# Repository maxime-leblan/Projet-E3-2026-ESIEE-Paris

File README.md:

# VigiZone : Prévention des collisions engins-piétons sur chantiers

*Remise du prix du meilleur projet technique lors du [Jour des Projets](https://jdp.esiee.fr) E3 2026 à ESIEE Paris*

### Membres de l'équipe

Nous étions une équipe de 6 étudiants en 1ère année du cycle ingénieur à ESIEE Paris
*dans l'ordre de droite à gauche :*
* Hugues JOUHAUD
* Naïm BEN-RAÏES
* Benoît DE KEYN
* Maxime LE BLAN
* Clarisse BLONDEL
* Jérémy FOUILLOUX

 Suivis par notre tutrice **Mme Ting WANG**, assistante professeur de robotique à ESIEE PARIS, nous avons reçu le prix du meilleur projet technique de la part du jury technique **M. Denis BUREAU** (tout à gauche sur la photo), professeur d'informatique à ESIEE Paris.

**[Lire le rapport complet du projet VigiZone (PDF)](https://drive.google.com/uc?export=download&id=16rXCA4nlOrGEzkfiPZYJjSept83bqB7f)**

---

## Contexte : Un enjeu de sécurité vital

Le secteur du Bâtiment et des Travaux Publics (BTP) fait face à des risques majeurs concernant la sécurité de ses travailleurs.
* Les collisions entre les engins de chantier et les ouvriers piétons représentent la première cause d'accidents mortels dans ce domaine.
* Selon l'Organisme Professionnel de Prévention du Bâtiment et des Travaux Publics (OPPBTP), on dénombre environ quinze décès par an causés par ces collisions.

Initialement, notre équipe souhaitait développer un dispositif pour les travailleurs isolés. Cependant, des échanges avec Monsieur Luc-Géry Helle, directeur régional génie civil de GTM Ouest (VINCI Construction France), ont mis en lumière une contrainte réglementaire stricte : la législation française interdit ou encadre très fortement le travail isolé sur les chantiers de construction. Le projet a donc été réorienté pour répondre au besoin critique de la prévention des collisions.

---

## Qu'est-ce que VigiZone ?

VigiZone est un système embarqué de détection en temps réel conçu pour éviter les collisions entre les ouvriers et les véhicules de chantier. 

Face à ce danger, les systèmes d'alarme sonores classiques (comme les bips de recul) perdent en efficacité, car les ouvriers s'habituent au bruit ambiant. De leur côté, les solutions basées sur des caméras IA ou des capteurs LiDAR sont extrêmement coûteuses et voient leurs performances chuter dans des conditions difficiles (poussière, boue, faible luminosité). 

C'est pourquoi VigiZone s'appuie sur la technologie **Ultra Wide Band (UWB)** :
* L'UWB offre une très haute précision de positionnement en se basant sur le temps de vol du signal.
* C'est un signal robuste capable de bien traverser les obstacles.

---

## Architecture et Utilisation

Le fonctionnement de VigiZone repose sur la communication entre trois sous-systèmes interdépendants :

* **Le Hub central (Unité de bord) :** Placé dans la cabine du conducteur et alimenté par la batterie de l'engin, il fusionne les données pour calculer les distances par trilatération. 

  Il est équipé d'un écran permettant de localiser les ouvriers en direct par rapport à une zone de danger et d'une alarme sonore.

* **Les Ancres (Boîtiers véhicule) :** Quatre capteurs disposés sur l'armature de l'engin (par exemple, aimantés) qui servent à localiser les ouvriers.
* **Le Tag (Boîtier ouvrier) :** Un équipement de protection individuelle (EPI) compact porté par l'ouvrier (sur son casque ou à la ceinture). Afin de garantir la sécurité, il ne possède aucun bouton d'arrêt et s'allume automatiquement.

**Scénario d'utilisation :** Si un ouvrier équipé d'un Tag pénètre dans une zone de danger virtuelle délimitée autour de l'engin, le système alerte instantanément les deux parties. Le conducteur est averti par l'écran et une alarme en cabine, tandis que le Tag de l'ouvrier déclenche une alerte sonore suffisamment puissante pour couvrir le bruit du chantier.

---

## Limites et Nuances du Système

Bien que la technologie UWB apporte une grande fiabilité de détection, notre solution technique ne prétend pas résoudre entièrement le problème des accidents. 

Comme nous l'a expliqué Monsieur Mathieu Baré, directeur prévention délégation génie civil Ouest chez VINCI Construction France, lors de notre visite sur le chantier du Grand Paris Express : plusieurs dispositifs de prévention existent, mais chacun possède ses avantages et ses limites selon les situations. À ce jour, aucun système ne permet de supprimer complètement le risque de collision entre engins et piétons. VigiZone doit donc être perçu comme un outil d'assistance et une couche de sécurité supplémentaire, qui vient compléter, mais en aucun cas remplacer, la vigilance indispensable des conducteurs et des ouvriers.

---

## En savoir plus

Pour consulter l'intégralité de notre démarche (choix technologiques, algorithmes de trilatération, conception des cartes sous KiCad et analyse éthique), nous vous invitons à lire notre rapport complet.

**[Lire le rapport complet du projet VigiZone (PDF)](https://drive.google.com/uc?export=download&id=16rXCA4nlOrGEzkfiPZYJjSept83bqB7f)**

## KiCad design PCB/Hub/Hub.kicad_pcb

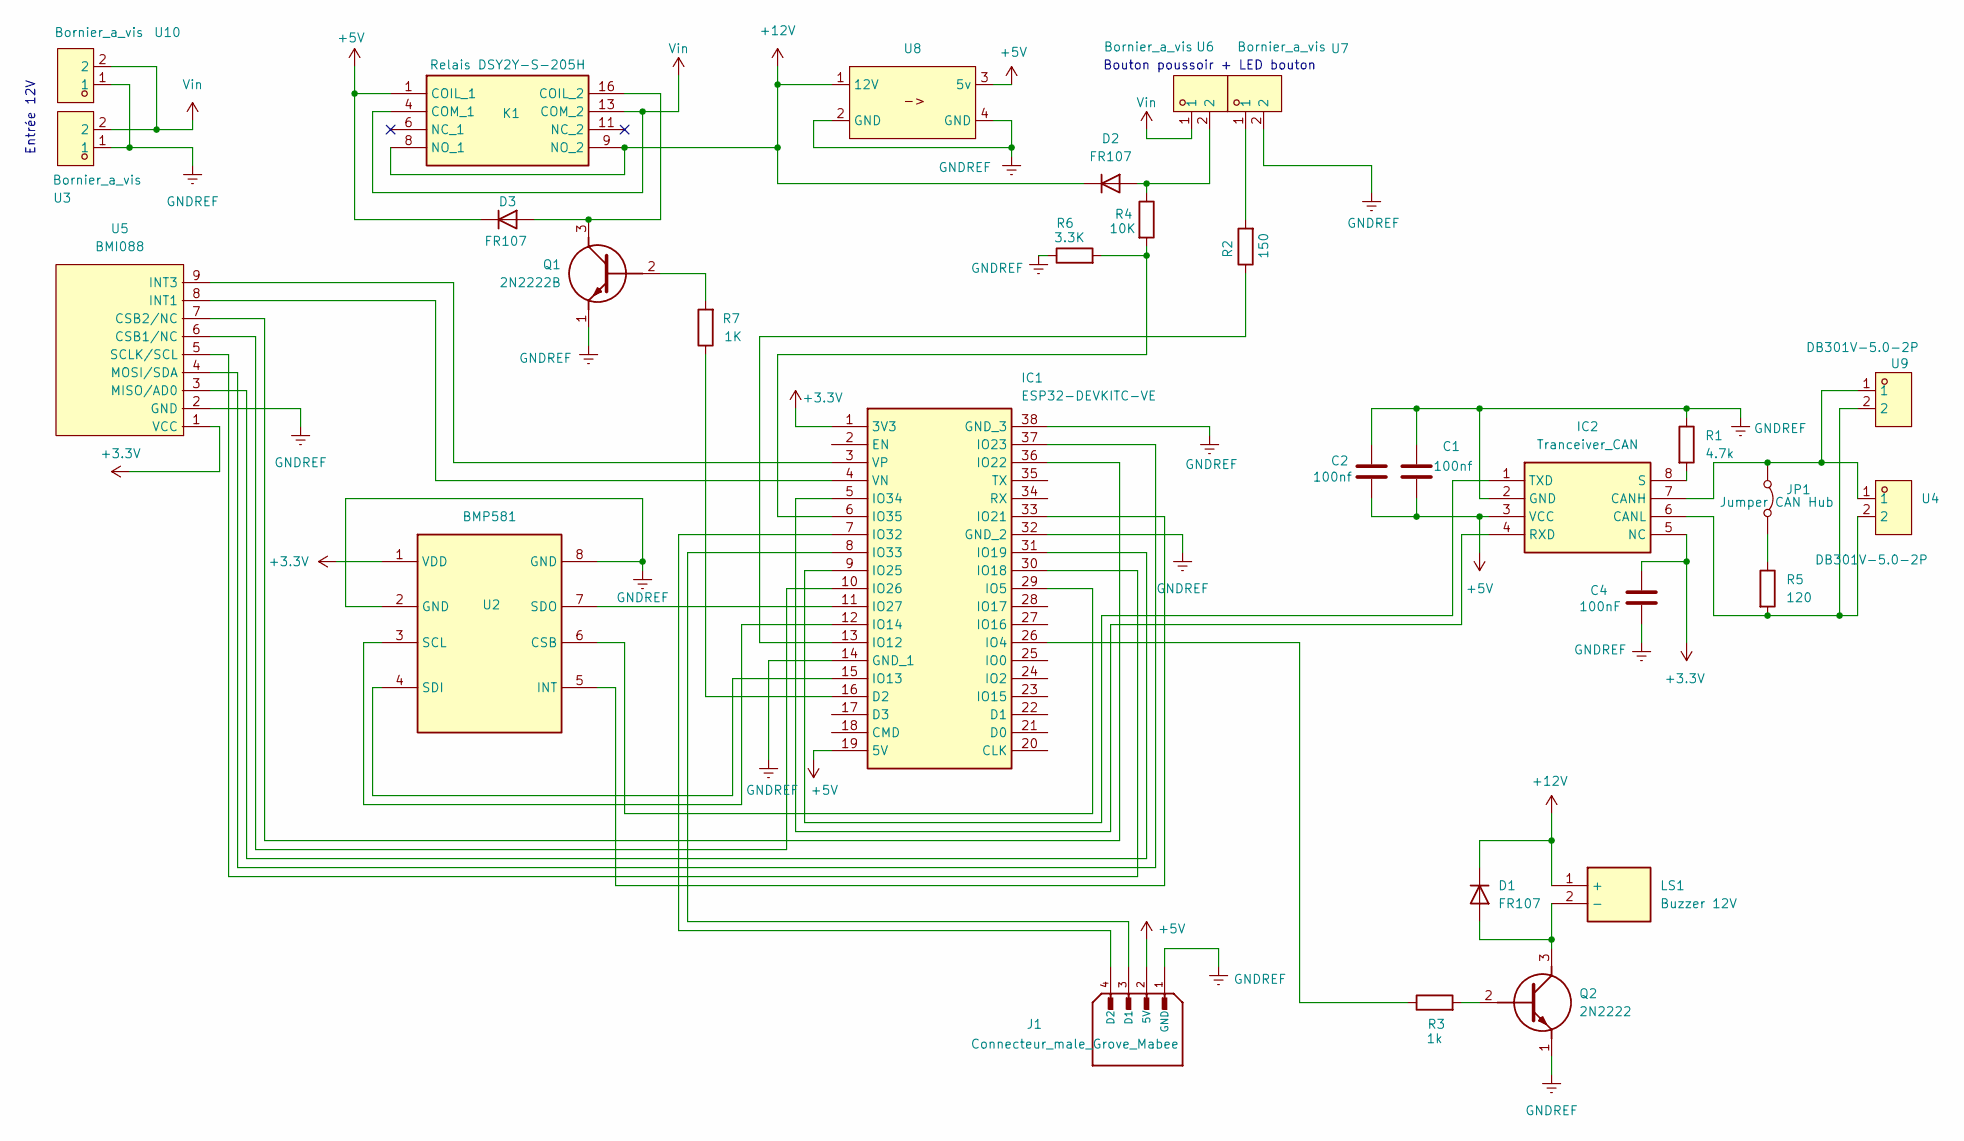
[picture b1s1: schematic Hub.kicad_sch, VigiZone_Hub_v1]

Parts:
C1, C2: 100nf; C_Axial_L3.8mm_D2.6mm_P7.50mm_Horizontal
C4: 100nF; C_0402_1005Metric_Pad0.74x0.62mm_HandSolder
D1, D2, D3: FR107; Diode FR107
IC1: ESP32-DEVKITC-VE; ESP32-WROVER DevKitC; Manufacturer_Part_Number ESP32-DEVKITC-VE; Mouser Part Number 356-ESP32-DEVKTC32VE
IC2: Tranceiver_CAN; Tranceiver CAN; Manufacturer_Part_Number TCAN1051VDRQ1; Mouser Part Number 595-TCAN1051VDRQ1
J1: Connecteur_male_Grove_Mabee; Connecteur male Grove_Mabee; PARTREV N/A
JP1: Jumper CAN Hub; Jumper CAN hub
K1: Relais DSY2Y-S-205H; Manufacturer_Part_Number DSY2Y-S-205L
LS1: Buzzer 12V; Manufacturer_Part_Number CMT-8504-100-SMT-TR; Mouser Part Number 490-CMT-8504100SMTTR
Q1: 2N2222B; Mouser Part Number 637-2N2222A
Q2: 2N2222; 2N2222B; Mouser Part Number 637-2N2222A
R1: 4.7k; R_Axial_DIN0207_L6.3mm_D2.5mm_P10.16mm_Horizontal
R2: 150; R_Axial_DIN0207_L6.3mm_D2.5mm_P10.16mm_Horizontal
R3: 1k; R_Axial_DIN0207_L6.3mm_D2.5mm_P10.16mm_Horizontal
R4: 10K; R_Axial_DIN0207_L6.3mm_D2.5mm_P10.16mm_Horizontal
R5: 120; R_Axial_DIN0207_L6.3mm_D2.5mm_P10.16mm_Horizontal
R6: 3.3K; R_Axial_DIN0207_L6.3mm_D2.5mm_P10.16mm_Horizontal
R7: 1K; R_Axial_DIN0207_L6.3mm_D2.5mm_P10.16mm_Horizontal
U2: BMP581; Manufacturer_Part_Number BMP581; Mouser Part Number 262-BMP581
U3, U6, U7, U10: Bornier_a_vis; Bornier a vis; MPN DB301V-5.0-2P-BU-S; LCSC Part C395882
U4, U9: DB301V-5.0-2P; Bornier a vis; MPN DB301V-5.0-2P-BU-S; LCSC Part C395882
U5: BMI088
U8: Abaisseur tension reglable

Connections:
+3.3V: C4.1, IC1.1 (3V3), IC2.5 (NC), U2.1 (VDD), U5.1 (VCC)
+5V: C1.2, C2.2, D3.1 (K), IC1.19 (5V), IC2.3 (VCC), J1.2 (5V), K1.1 (COIL_1), U8.3 (5v)
+12V: D1.1 (K), D2.1 (K), K1.8 (NO_1), K1.9 (NO_2), LS1.1 (+), U8.1 (12V)
GNDREF: C1.1, C2.1, C4.2, IC1.14 (GND_1), IC1.32 (GND_2), IC1.38 (GND_3), IC2.2 (GND), J1.1 (GND), Q1.1 (E), Q2.1 (E), R1.1, R6.1, U2.2 (GND), U2.8 (GND), U3.1, U5.2 (GND), U7.2, U8.2 (GND), U8.4 (GND), U10.1
unnamed: D1.2 (A), LS1.2 (-), Q2.3 (C)
unnamed: D2.2 (A), R4.1, U6.2
unnamed: D3.2 (A), K1.16 (COIL_2), Q1.3 (C)
unnamed: IC1.16 (D2), R7.1
unnamed: IC1.26 (IO4), R3.1
unnamed: IC1.29 (IO5), U2.6 (CSB)
unnamed: IC1.13 (IO12), R2.1
unnamed: IC1.15 (IO13), U2.4 (SDI)
unnamed: IC1.12 (IO14), U2.3 (SCL)
unnamed: IC1.30 (IO18), U5.5 (SCLK/SCL)
unnamed: IC1.31 (IO19), U5.3 (MISO/AD0)
unnamed: IC1.33 (IO21), U2.5 (INT)
unnamed: IC1.36 (IO22), U5.7 (CSB2/NC)
unnamed: IC1.37 (IO23), U5.4 (MOSI/SDA)
unnamed: IC1.9 (IO25), IC2.1 (TXD)
unnamed: IC1.10 (IO26), U5.6 (CSB1/NC)
unnamed: IC1.11 (IO27), U2.7 (SDO)
unnamed: IC1.7 (IO32), J1.4 (D2)
unnamed: IC1.8 (IO33), J1.3 (D1)
unnamed: IC1.5 (IO34), IC2.4 (RXD)
unnamed: IC1.6 (IO35), R4.2, R6.2
unnamed: IC1.4 (VN), U5.8 (INT1)
unnamed: IC1.3 (VP), U5.9 (INT3)
unnamed: IC2.7 (CANH), JP1.1 (A), U4.1, U9.1
unnamed: IC2.6 (CANL), R5.2, U4.2, U9.2
unnamed: IC2.8 (S), R1.2
unnamed: JP1.2 (B), R5.1
unnamed: Q1.2 (B), R7.2
unnamed: Q2.2 (B), R3.2
unnamed: R2.2, U7.1
Vin: K1.4 (COM_1), K1.13 (COM_2), U3.2, U6.1, U10.2

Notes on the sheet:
Entrée 12V
Bouton poussoir + LED bouton

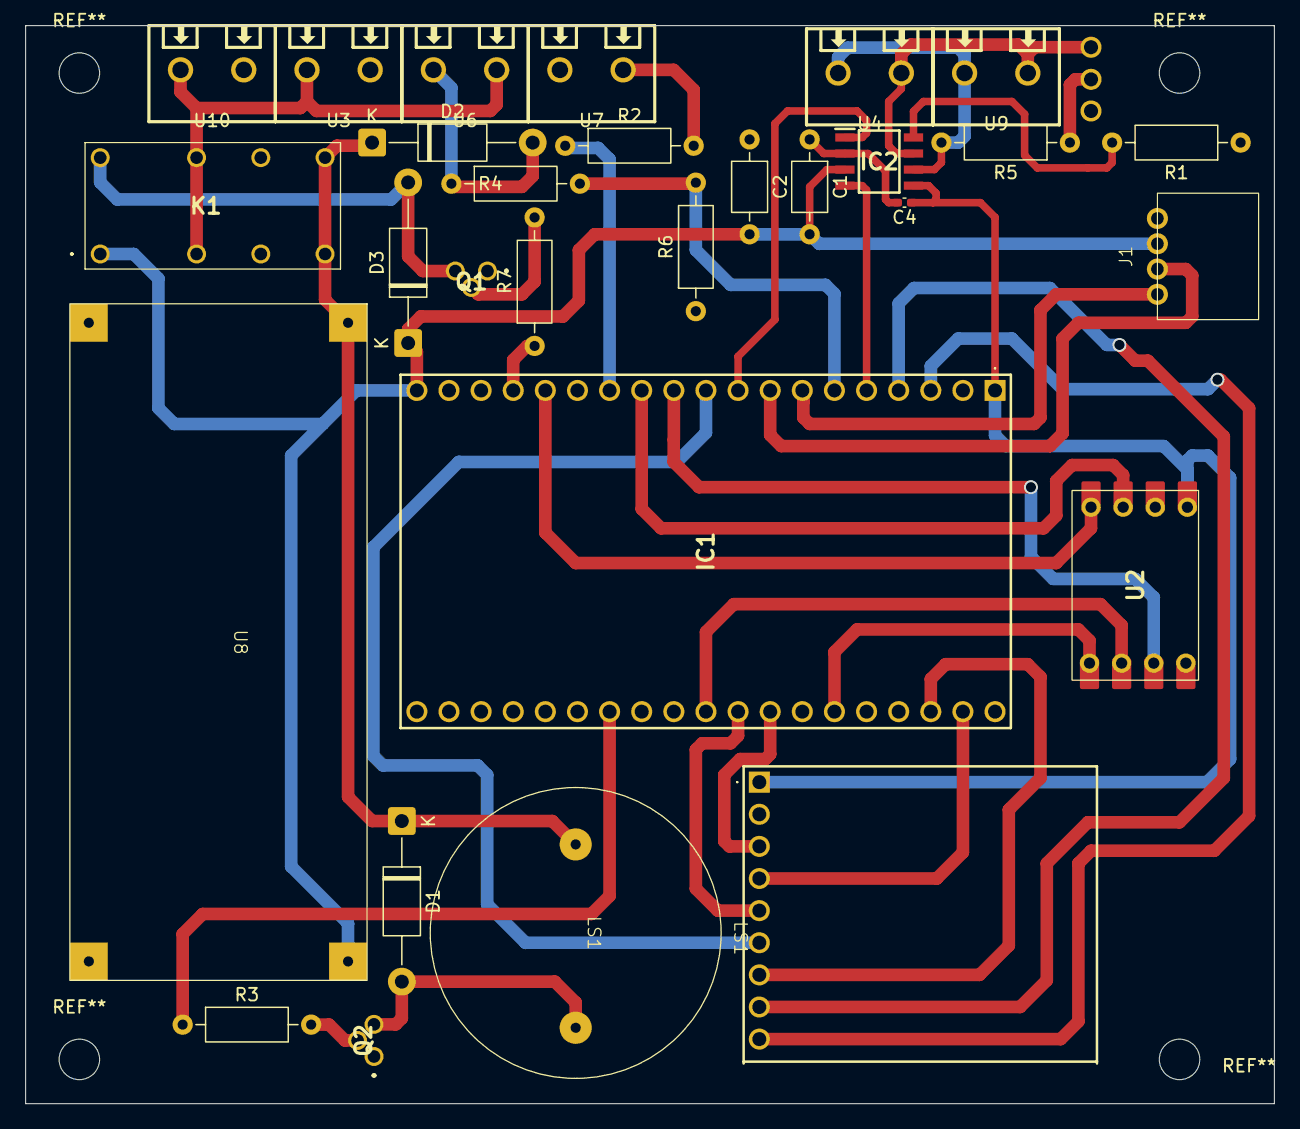
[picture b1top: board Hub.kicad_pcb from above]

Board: 2 copper layers, 98.8 x 85.2 mm, 30 parts (0 on the bottom side), 35 nets.

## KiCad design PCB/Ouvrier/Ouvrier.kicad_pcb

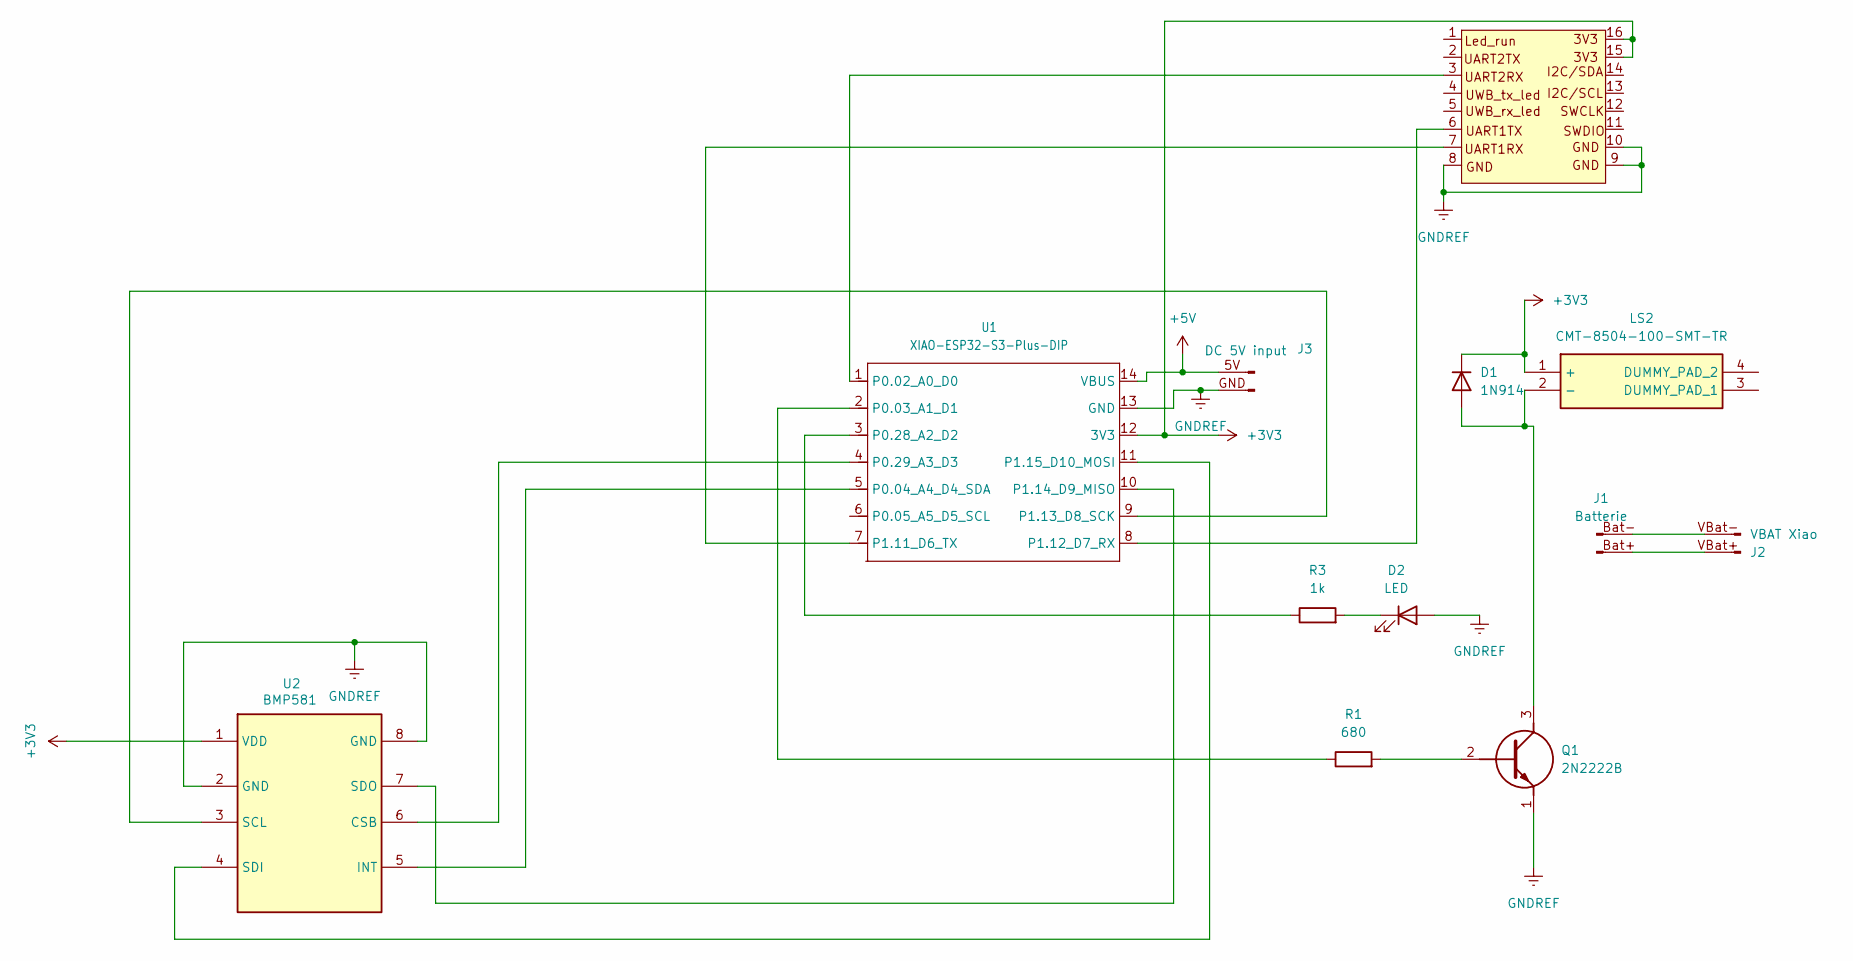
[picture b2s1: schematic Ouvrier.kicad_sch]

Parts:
D1: 1N914; D_DO-35_SOD27_P7.62mm_Horizontal
D2: LED; LED_D3.0mm_Clear
J1: Batterie
J2: VBAT Xiao; Raccord VBat XIAO
J3: DC 5V input; chargeur sans fil
LS2: CMT-8504-100-SMT-TR; Buzzer CMS; Manufacturer_Part_Number CMT-8504-100-SMT-TR; Mouser Part Number 490-CMT-8504100SMTTR
Q1: 2N2222B; Mouser Part Number 637-2N2222A
R1: 680; R_Axial_DIN0207_L6.3mm_D2.5mm_P10.16mm_Horizontal
R3: 1k; R_Axial_DIN0207_L6.3mm_D2.5mm_P10.16mm_Horizontal
U1: XIAO-ESP32-S3-Plus-DIP; XIAO nRF52840 sense plus
U2: BMP581; Manufacturer_Part_Number BMP581; Mouser Part Number 262-BMP581
U3: UWB; maUWB chipset

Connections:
+3V3: D1.1 (K), LS2.1 (+), U1.12 (3V3), U2.1 (VDD), U3.15 (3V3), U3.16 (3V3)
+5V: J3.5V (GND), U1.14 (VBUS)
GNDREF: D2.2 (A), J3.GND, Q1.1 (E), U1.13 (GND), U2.2 (GND), U2.8 (GND), U3.8 (GND), U3.9 (GND), U3.10 (GND)
unnamed: D1.2 (A), LS2.2 (-), Q1.3 (C)
unnamed: D2.1 (K), R3.2
unnamed: J1.Bat- (Pin_1), J2.VBat-
unnamed: J1.Bat+ (Pin_2), J2.VBat+
unnamed: Q1.2 (B), R1.2
unnamed: U1.1 (P0.02_A0_D0), U3.3 (UART2RX)
unnamed: R1.1, U1.2 (P0.03_A1_D1)
unnamed: U1.5 (P0.04_A4_D4_SDA), U2.5 (INT)
unnamed: R3.1, U1.3 (P0.28_A2_D2)
unnamed: U1.4 (P0.29_A3_D3), U2.6 (CSB)
unnamed: U1.7 (P1.11_D6_TX), U3.7 (UART1RX)
unnamed: U1.8 (P1.12_D7_RX), U3.6 (UART1TX)
unnamed: U1.9 (P1.13_D8_SCK), U2.3 (SCL)
unnamed: U1.10 (P1.14_D9_MISO), U2.7 (SDO)
unnamed: U1.11 (P1.15_D10_MOSI), U2.4 (SDI)

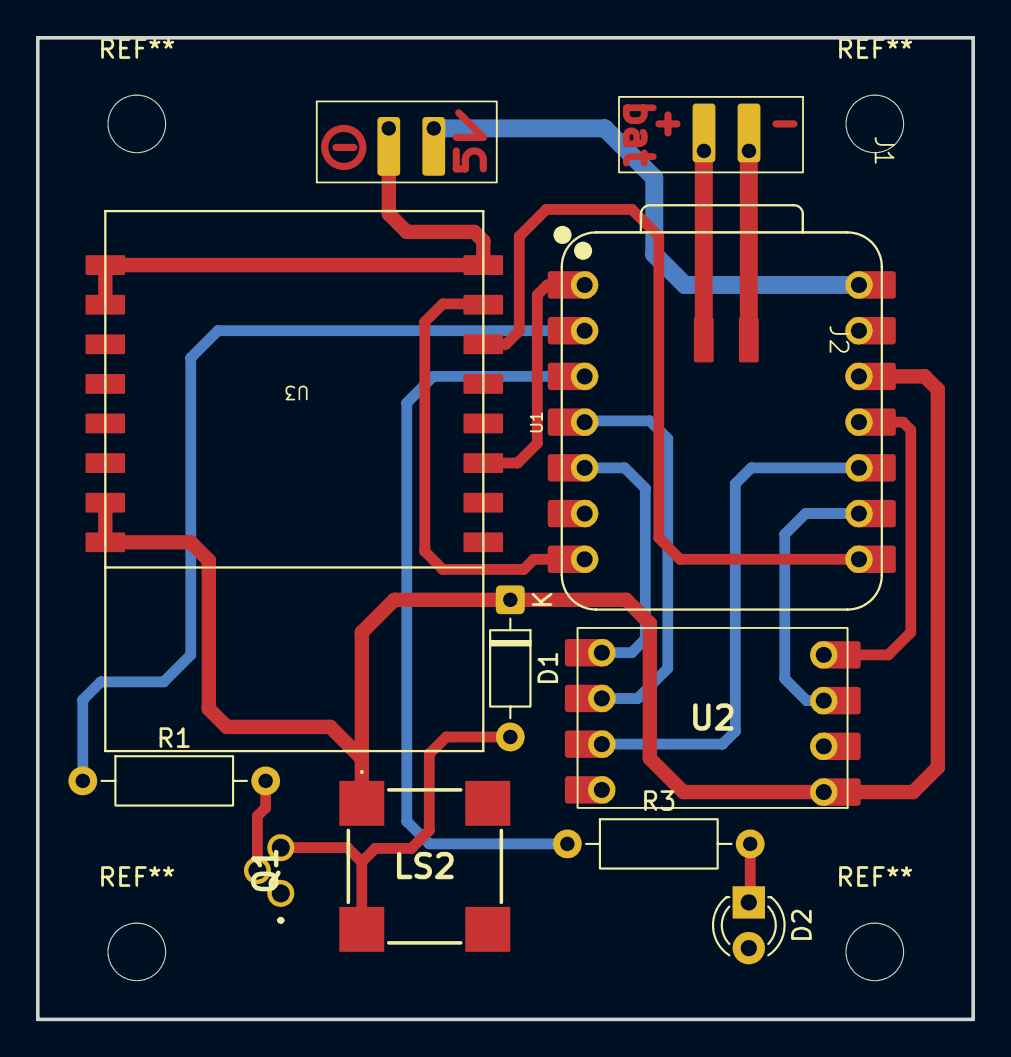
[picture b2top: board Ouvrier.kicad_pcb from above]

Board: 2 copper layers, 52.0 x 54.5 mm, 12 parts (0 on the bottom side), 18 nets.

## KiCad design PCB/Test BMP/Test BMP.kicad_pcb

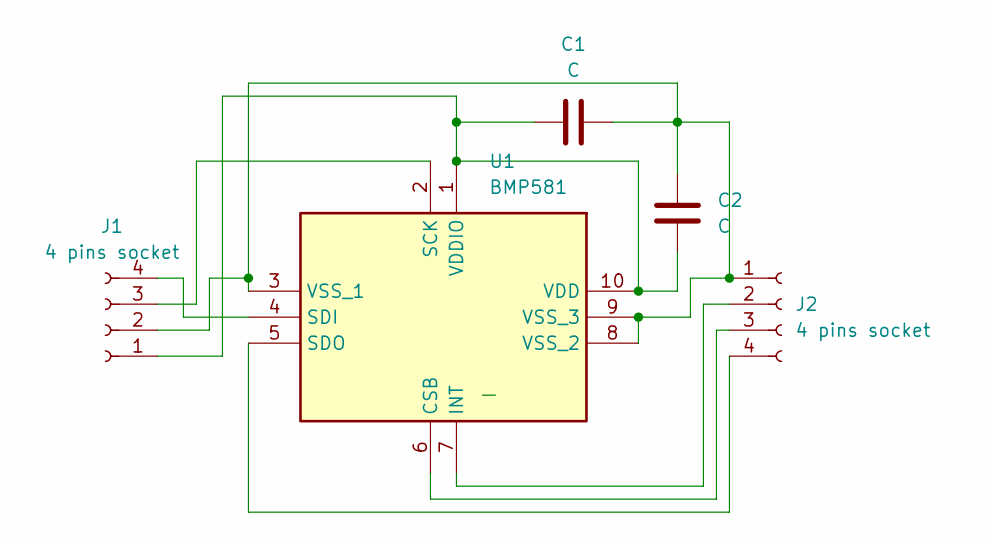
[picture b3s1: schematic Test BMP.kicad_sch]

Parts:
C1, C2: C; C_0402_1005Metric_Pad0.74x0.62mm_HandSolder
J1, J2: 4 pins socket
U1: BMP581; Manufacturer_Part_Number BMP581; Mouser Part Number 262-BMP581

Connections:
unnamed: C1.2, C2.2, J1.1, U1.1 (VDDIO), U1.10 (VDD)
unnamed: C1.1, C2.1, J1.2, J2.1, U1.3 (VSS_1), U1.8 (VSS_2), U1.9 (VSS_3)
unnamed: J1.3, U1.2 (SCK)
unnamed: J1.4, U1.4 (SDI)
unnamed: J2.2, U1.7 (INT)
unnamed: J2.3, U1.6 (CSB)
unnamed: J2.4, U1.5 (SDO)

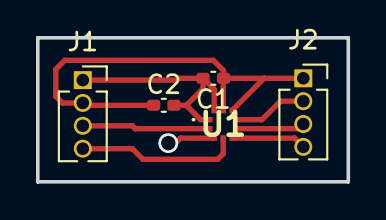
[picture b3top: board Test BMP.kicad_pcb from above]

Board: 2 copper layers, 17.2 x 8.0 mm, 5 parts (0 on the bottom side), 7 nets.

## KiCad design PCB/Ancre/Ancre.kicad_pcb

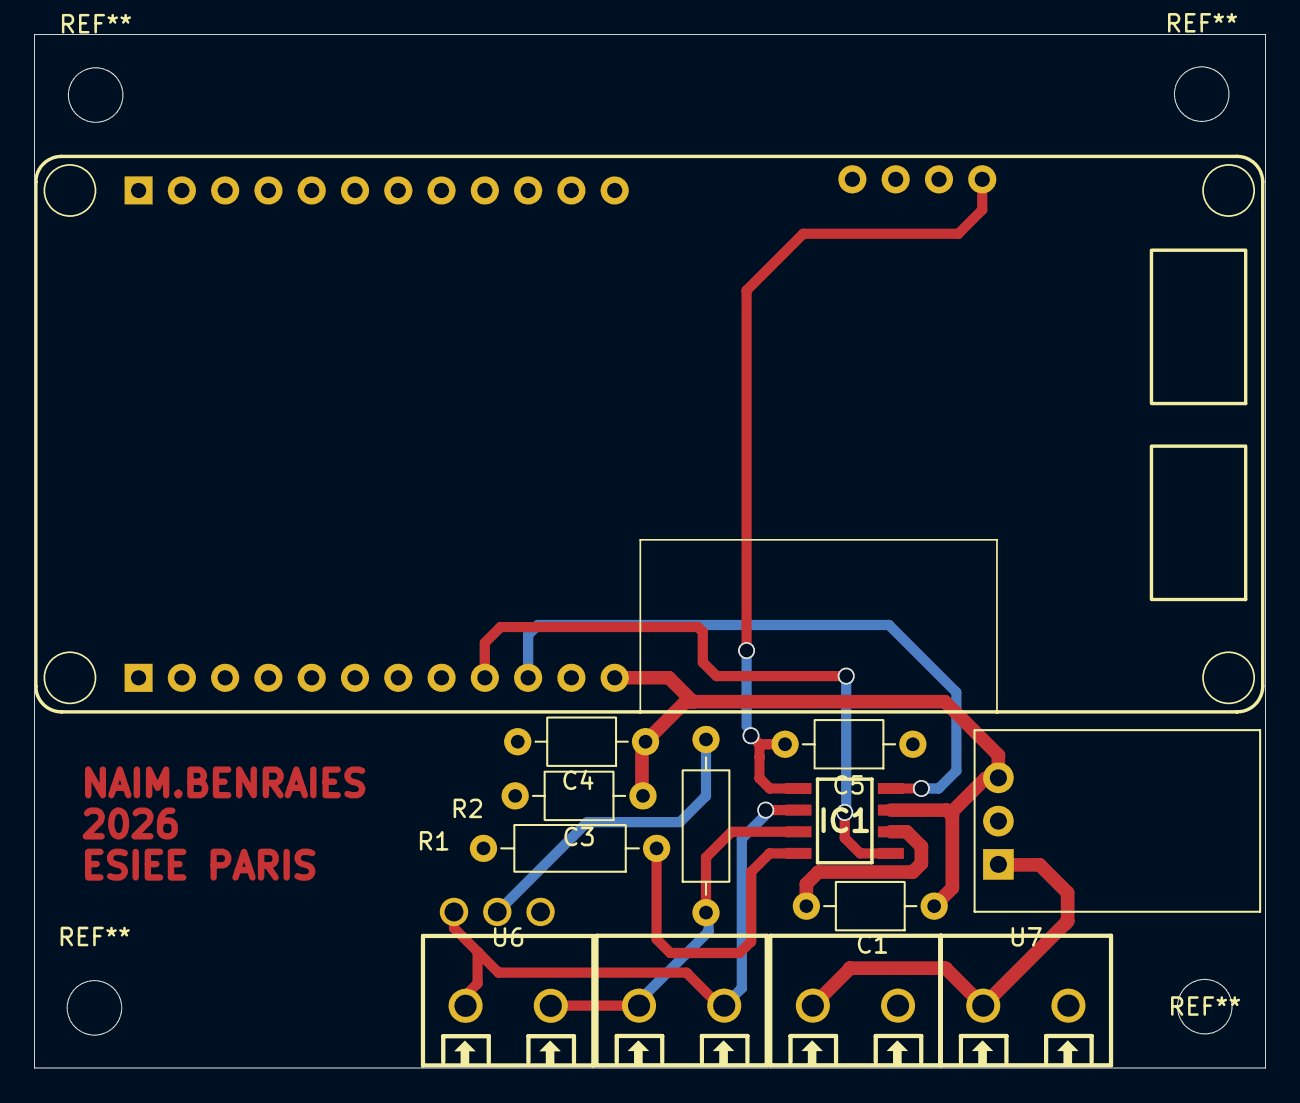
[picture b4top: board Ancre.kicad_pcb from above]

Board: 2 copper layers, 72.2 x 60.7 mm, 14 parts (0 on the bottom side), 10 nets.

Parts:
C1: 10uF; C_Axial_L3.8mm_D2.6mm_P7.50mm_Horizontal
C3, C4, C5: 100nF; C_Axial_L3.8mm_D2.6mm_P7.50mm_Horizontal
IC1: TCAN1051VDRQ1; SOIC127P600X175-8N (1)
R1: R; R_Axial_DIN0207_L6.3mm_D2.5mm_P10.16mm_Horizontal
R2: 120; R_Axial_DIN0207_L6.3mm_D2.5mm_P10.16mm_Horizontal
U1: OKI-78SR-5_1.5-W36-C; Abaisseur 5v OKI
U2, U3: DB301V-5.0-2P; CONN-TH_2P-P5.00_L7.6-W10.0 (1)
U4: maUWB ESP32-S3 AT
U5: JUMPER CAN
U6, U7: DB301V-5.0-2P; Bornier a vis

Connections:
+5V: C1.1, C3.1, C4.1, IC1.3 (VCC), U1.3 (OUT), U4.13 (VDD)
+12V: U1.1 (IN), U2.1, U7.1
GNDREF: C1.2, C3.2, C4.2, C5.1, IC1.2 (GND), R1.2, U1.2 (GND), U2.2, U4.2 (GND), U4.14 (GND), U4.25 (GND), U7.2
unnamed: IC1.7 (CANH), R2.1, U3.1, U6.2
unnamed: IC1.6 (CANL), U3.2, U5.J2 (CAN_line), U6.1
unnamed: C5.2, IC1.5 (NC), U4.28 (3V3)
unnamed: IC1.4 (RXD), U4.15 (RXD)
unnamed: IC1.8 (S), R1.1
unnamed: IC1.1 (TXD), U4.16 (TXD)
unnamed: R2.2, U5.J1 (Resistance)

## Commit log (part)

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2026-06-08 Implémentation fonction rotation plan
    Implémentation de fonctions pour appliquer une rotation en 3D sur une liste de points + ajout de nouveaux opérateurs * dans la classe V3.
2026-06-08 Ouvrier_v4_test_DRC
2026-06-08 Ancre_v13_test_DRC
2026-06-08 HUB_V4_test_DRC
2026-06-08 Generation gbr TEST
2026-06-08 batterie et Induction
2026-06-08 GBR ANCRE
2026-06-08 ouvrier_v6
2026-06-08 Ouvrier_v7
2026-06-08 Ajout fonctions
    Calcule le centre géométrique des 4 ancres en faisant la moyenne de leurs coordonnées.
    Calcule la distance de chaque tag par rapport au centre des ancres,
    Trie la liste du plus proche au plus lointain, et l'envoie via UART (Serial).
    Creation du plan et du choix des points
2026-06-08 Implémentation du moteur de visualisation 3D pour les tests
    Implémentation du code permettant de visualiser à l'écran les test des fonctions 3D.
2026-06-10 Bugfix : maintenant compile
2026-06-10 update bibliotheque KiCad
2026-06-10 Modification du programme de test ESP32 WROVER
2026-06-10 Ouvrier_v8
2026-06-10 Première mise en page du rapport
    Création du fichier d'entête header.tex qui contient tous les packages à inclure, et création de main.tex qui rassemblera le code de toutes les sections du rapport. Création d'un premier sommaire dan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
2026-06-11 Mis à jour gitignore LateX
2026-06-11 Implémentation translation ancre
    Implémentation de la fonction permettant de déplacer les ancres au niveau de l'origine du repère tel que leur épicentre ait pour coordonnées (0, 0, 0). Ajout de fonctionnalités dans UWBModuleList et 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
2026-06-11 update gitignore build et vscode
2026-06-11 Ajout de std:: devant les map. pour indiquer que c'est C++ et non Arduino
2026-06-11 Implémentation changement de base
2026-06-11 Mise à jour du main.cpp du Hub
2026-06-11 Ajout morceau wifi
2026-06-11 MaJ Bibliotheque_Projet fp-lib-table
2026-06-11 changement transistor 2N2222 (empreinte)
2026-06-11 MaJ bibliotheque KiCad jumper et connecteur mabee
2026-06-11 MaJ bibliotheque KiCad Hub
2026-06-11 MaJ composants Hub empreinte et schematic
2026-06-11 rennomage Hub KiCad
2026-06-12 Diode Bibliothèque KiCad
2026-06-12 MaJ Hub nouvelle version relais-bouton-alim
2026-06-12 MaJ visuelle schematic Hub KiCad
2026-06-12 Initialisation SafeZone + Ancres
2026-06-12 Mise à jour main du Hub
    Ajout de fonctions d'affichages textuelle dans toutes les classes + affichage de la liste des ancres et de la zone de sécurité dans le moniteur série
2026-06-12 Validation sch HUB OUVRIER
2026-06-12 Ouvrier_v10_PCB
2026-06-12 Correction extraction de donnée de la Flash du Hub
2026-06-12 Push temporaire communication entre ESP32
2026-06-12 Ajout dossier algo final ancre
2026-06-12 connected INT pins BMI088 KiCad Hub
2026-06-12 Pin INT BMPA581 connecté KiCad Hub
2026-06-12 MaJ KiCad Ouvrier
    pin INT BMP et raccord batterie
2026-06-12 MaJ KiCad Ouvrier (aucun changement)
2026-06-14 Démarrage partie Software du rapport + personnalisation table des matières
2026-06-15 Réorganisation arborescence fichiers MessageManager pour hub
2026-06-15 Implémentation code communication Wifi Hub
2026-06-15 Ouvrier_Version_Finale_PCB
2026-06-15 Creation Fichier Drill Ouvrier HUB
2026-06-15 Modification librairie Wifi + UART pour le Hub
2026-06-15 Fonctionnement des ancres et comm
2026-06-15 mise en place template projet
2026-06-15 v1 Finale librairie communication Wifi + UART
2026-06-15 Preparation du hub a recevoir des messages des ancres sur le ESP NOW
2026-06-16 MAJ librairie communication UART
2026-06-16 Ajout d'ignore file pour compiler et tester
2026-06-16 Fonctionnement du monitor ancre, et println de l'adresse MAC
2026-06-16 Création des fichiers pour la communication CAN Hub avec Ancres
2026-06-16 bibliothèque fusion Madgwick filter
2026-06-16 Template Rapport
2026-06-16 Filtre Madgiwck fonctionnel
2026-06-16 BMP naim
2026-06-16 Template_bibli
2026-06-16 Fonctionnement avec plusieurs ancres, et bonne adresse MAC
2026-06-16 Petit changements pour choix du mode de communication
2026-06-16 exemple vecteur gravité simplifié
2026-06-16 version avec etalonnage BMI088 vecteur Gravité
2026-06-16 Mesure IMU : utilisation d'un timer hardware pour optimiser le coeur 0
    en fait la mesure puis calcule avec le filtre de Madgwick ne prend que 90µs (au pire 670 au démarrage), or ça sert à rien qu'il s'exécute à plus de 400Hz (pcq la plupart de vibrations hautes frequenc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
    Donc comme ça, toutes les 2,5ms (400HZ), la valeur du vecteur gravité est mise à jour en mutex rapidement puis la tache est freeze pour laisser p=les autre taches s'executer peu importe leur priorité.
2026-06-17 MAJ librairie CAN + création code initialisation position ancre
2026-06-17 test XIAO
2026-06-17 Implémentation finale InitAnchorPosition
2026-06-17 Réaménagement des dossiers de librairie pour PlatformIO
2026-06-17 Compilation avec librairie can
2026-06-17 Ancre recompile
2026-06-17 Meilleure séparation entre Gestion des Ancres et WifiManager, correction bugs
2026-06-17 Finaliation code initialisation position ancre côté code des Ancres
2026-06-17 test qui marche pas
2026-06-17 Séparation des codes dans le main pour clarté.
2026-06-18 Ecran : Communication avec Hub
2026-06-18 Implémentation librairie communication UWB tag - ancre
2026-06-18 Fonctionnement de l'écran et main de l'hub
2026-06-18 MAJ librairie communication UWB pour XIAO
2026-06-18 Clear des tags de l'écran lorsque nécessaire
2026-06-18 Ca compile xd
2026-06-18 Réparation plantage plateformio.ini algo tag
2026-06-18 Corrections bugs
2026-06-18 Implémentation interuption XIAO + UWB
2026-06-19 Image Poster zone de sécurité
2026-06-19 Réorganisation fichiers ouvriers
2026-06-19 Correction : tag envoyé
2026-06-19 Changement étirement lors de correction, déplacement des points
2026-06-19 Maintenant c'est la bonne
2026-06-19 La c bon jpense
2026-06-19 Clear des configutations côté hub
2026-06-19 Correction platformio.ini pour compiler (fonctionne toujours pas)
2026-06-19 Le code du tag COMPILE ENFIN
2026-06-19 Correction initialisation tag
2026-06-19 Micro correction
2026-06-19 Correction bouton stop
2026-06-19 Ajout nouvelle fonction communication CAN
2026-06-19 Correction communication UWB + ouvrier
2026-06-19 Modif documentation
2026-06-19 Création main final hub
2026-06-19 Update avec CAN
2026-06-20 Version finale bibliotheque Capteur de pression
2026-06-20 intégration lecture pression dans le code de l'ouvrier
2026-06-20 correction bouton PCB Kicad
2026-06-20 Code main hub final débogué EN THEORIE
2026-06-20 Déplacement code Hugues
2026-06-20 ouvrier
2026-06-20 MAJ code hub + UWBMessageManager
2026-06-20 Code Final main Ancre EN THEORIE
2026-06-20 Ouvrier_Fct_calcul_BatteryLow
2026-06-21 Correction code ancre pour compilation
2026-06-21 Update_main.cpp_Hub
2026-06-21 mise en place de commentaire
2026-06-21 Correction problèmes CAN
2026-06-21 Code test Xiao UWB
2026-06-21 Correction CAN main hub
2026-06-21 Algo de test pour le CAN
2026-06-22 Correction CANMessageManager
2026-06-22 Création test CAN sur 2 ancres
2026-06-22 Changement receiveCANMessage
2026-06-22 test qui fonctionnera d'apres hugus
2026-06-22 re push ini
2026-06-22 test ancre
2026-06-22 Nouveaux tests fonctionnels XIAO UWB
2026-06-22 Modification CAN (ça marche partout)
2026-06-22 tentative de compilation
2026-06-22 MAJ CAN librairie
2026-06-22 Update UWBmessagemanager
2026-06-22 update UWB
2026-06-22 MAJ main tag
2026-06-22 En vrai on s'en fout
2026-06-22 nouvelle initialisation UWB ancre
2026-06-22 MAJ initialisation tag UWB
2026-06-22 Ajout commentaire test tag
2026-06-22 essai de polling du hub à l'ancre 0 pour trilateration
2026-06-22 Problème UWB
2026-06-22 MAJ tag
2026-06-22 MAJ tag affichage OK
2026-06-22 Test Ancre - Ouvrier AT RaNGE
    L'ancre n'est toujours pas captée par le tag UWB malgré son broadcast fonctionnel
2026-06-23 La carte existe maintenant.
2026-06-23 MAJ code main ouvrier
2026-06-23 Modifications fonctionnements libs avec polling
2026-06-23 MAJ code ouvrier
2026-06-23 Code Ancre fonctionnel affichage OLED
2026-06-23 Code Ancre et Hub CAN/UWB fonctionnel Polling
2026-06-23 MAJ trilatération main Hub
2026-06-23 logs Hub trilateration
2026-06-23 fix conversion distances
2026-06-23 MAJ main Hub
2026-06-23 logs debug ecran Hub
2026-06-23 Ajout sendATCommandWithResult + MAJ ancre
2026-06-23 Fix ecran, chgmts noms variables
2026-06-23 Ajout logs init ancres
2026-06-23 MAJ init phase Ancre
2026-06-23 TestInitAncres
2026-06-23 Code ANCRE pour l'initialisation des ancres
2026-06-23 MAJ code hub init ancres
2026-06-23 mise a jour ouvrier fonction charge
2026-06-23 Ajout logs ANcre init
2026-06-23 MAJ toggleUWBMode ancre + init ancres hub
2026-06-23 Suppression RESTORE ancres
2026-06-23 Oscilloscope UWB
    Permet d'intergagir en live (Rx et TX) avec un UWB d'une carte Makerfabs
2026-06-23 COde de lecture coté ancre fixé
    parsing At range amélioré coté ancre
2026-06-24 Hardcodage distance entre ancres
2026-06-24 MAJ code init ancres positions hub
2026-06-24 Ajout tri id liste modules UWB
2026-06-24 Selection Tag Application etalonnage
2026-06-24 Ajout logs
2026-06-24 Modif hardcoding
2026-06-24 Ajout de log pour extraction Flash
2026-06-24 Hardcode nouvelles distances ancres
2026-06-24 fix getCoordonnee fonction bloquante
2026-06-24 Amélioration descente gradient init ancres
2026-06-24 Re commit descente de gradient
2026-06-24 Correction gradient descente APRES bug tag4
2026-06-24 hub_alarme_test
2026-06-24 Fix Maxime Ancres Etalonnage
2026-06-24 Nouvelle mesure harcoding init ancres
2026-06-24 debug position tag en live
2026-06-24 MAJ mesures distances ancres tétraèdre "régulier"
2026-06-24 Nouvelle fonction hardcode ancres
2026-06-24 test
2026-06-24 Update main.cpp
    Ca Refonctionne Ca normalement
2026-06-24 Ajout log main hub DISTMAP
2026-06-24 No warning
2026-06-24 Code Pression Tag vers Ancre master
2026-06-24 Ya des changements à faire mais jsp quoi donc bon
2026-06-24 FIX algorithme trilatération
2026-06-24 serial
2026-06-24 FichiersVide
2026-06-24 code ouvrier fonctionnel intermittent
2026-06-24 fonction réglage buzzer
2026-06-24 CALIBRATION
2026-06-25 charge rapide batterie
2026-06-26 MAJ programme de test trilatération
2026-06-26 partie_commune
2026-06-26 margin
2026-06-26 conflict
2026-06-26 MAJ partie Software
2026-06-26 hardware
2026-06-26 Ajout image raylib
2026-06-26 MAJ gitignore
2026-06-26 update hardware
2026-06-26 MAJ software trilatération
2026-06-27 new file
2026-06-27 Create main.synctex(busy)
2026-06-27 Suppression fichiers du Gitignore
2026-06-27 Suppression fichiers du Gitignore 2
2026-06-27 Update Gitignore
2026-06-27 upddate sample.bib
2026-06-27 update_margin
2026-06-27 Commit site 1 naim
2026-06-27 update title
2026-06-27 fichier modelisation 3D
2026-06-27 v1 3D
2026-06-27 ajout screen Naim Fucsion360
2026-06-27 french
2026-06-27 add sch
2026-06-27 capture bambulab
2026-06-28 figure giy hub
2026-06-28 babel anglais ET francais
2026-06-28 MAJ software MDS
2026-06-28 Creation du plan
2026-06-29 Schémas Rapport choix des composants
2026-06-29 gestion de projet V2
2026-06-29 Gestion Projet V3
2026-06-29 v1 choix des composants
2026-06-29 update HUB
2026-06-29 MAJ Software Changement de base
2026-06-29 reference 3D et Gestion Projet
2026-06-29 update figure
2026-06-29 Ajout protocoles communication
2026-06-29 suppression bbl et blg
2026-06-29 figure
2026-06-29 MAJ Software CAN
2026-06-29 Specifications et Objectifs
2026-06-29 MAJ Software protocole UWB
2026-06-29 Ajout Ecran
2026-06-29 Outil et Environnement de travail
2026-06-29 MaJ avantages GitHub
2026-06-29 Sauvegarde rapport Choix composants
2026-06-29 test1
2026-06-29 Correction Mise en page Images Software
2026-06-29 Modification références
2026-06-29 Etude_preliminaire.tex
2026-06-29 paragraph vers subsubsection
2026-06-29 MAJ Software référence
2026-06-29 Gestion de Projet placé et Choix de la tech FINAL
2026-06-29 Projets similaires existants
2026-06-29 Maj Choix composants
2026-06-29 ajout photo
2026-06-29 Ajout partie Clarisse
2026-06-29 MAJ Clarisse
2026-06-29 ajout tab choix tech
2026-06-29 updayte partie commune
2026-06-29 Choix composants finalisé
2026-06-29 Ajout gravite pression
2026-06-29 Changements
2026-06-29 Setup du système.
2026-06-29 Ajout Abstract
2026-06-29 Suppression latin
2026-06-29 Ajout photos
2026-06-29 Maj capteur pression et gravité
2026-06-29 Ajout résultats
2026-06-29 MaJ Readme avec le rapport sur Drive
    Le rapport dépasse 100MB il ne peut donc pas être ajouté au GitHub sans activé git LFS qui est contraignant.
2026-06-29 MaJ readme
